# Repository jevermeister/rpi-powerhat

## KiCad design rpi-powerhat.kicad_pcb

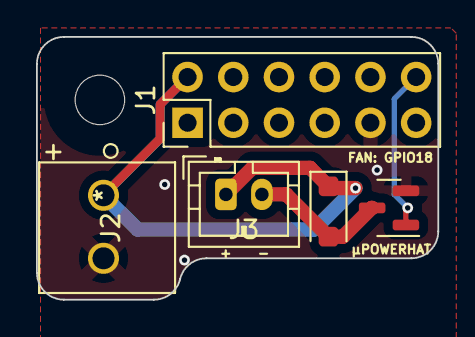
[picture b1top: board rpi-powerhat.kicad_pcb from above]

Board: 2 copper layers, 22.3 x 14.6 mm, 5 parts (0 on the bottom side), 4 nets.

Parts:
D1: D; D_SOD-123F
J1: rpi-gpio-powerhat; PinHeader_2x06_P2.54mm_Vertical
J2: VIN; 1546551-2
J3: FAN; JST_PH_B2B-PH-K_1x02_P2.00mm_Vertical
Q2: AO3402; SOT-23

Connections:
+5V: D1.1 (K), J1.2 (5V), J2.1, J3.1
/rpi-gpio-powerhat/GPIO18-: D1.2 (A), J3.2, Q2.3 (D)
GND: J1.9 (GND), J2.2, Q2.2 (S)
GPIO18: J1.12 (BCM18_PCM_C), Q2.1 (G)

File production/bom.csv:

Designator,Footprint,Quantity,Value,LCSC Part #
,RPi_Hat_Mounting_Hole,1,,
D1,D_SOD-123F,1,D,C64898
J1,PinHeader_2x06_P2.54mm_Vertical,1,rpi-gpio-powerhat,
J2,1546551-2,1,VIN,
J3,JST_PH_B2B-PH-K_1x02_P2.00mm_Vertical,1,FAN,
Q2,SOT-23,1,AO3402,C351406

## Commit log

2023-03-11 Renamed project, removed unused stuff and added measurements
2023-03-21 Made the powerhat even smaller
2023-03-21 Added more vias
2023-07-21 Added recent changes and production files

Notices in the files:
parts and their libraries:
Copyright 2021 Accelerated Designs. All rights reserved.
